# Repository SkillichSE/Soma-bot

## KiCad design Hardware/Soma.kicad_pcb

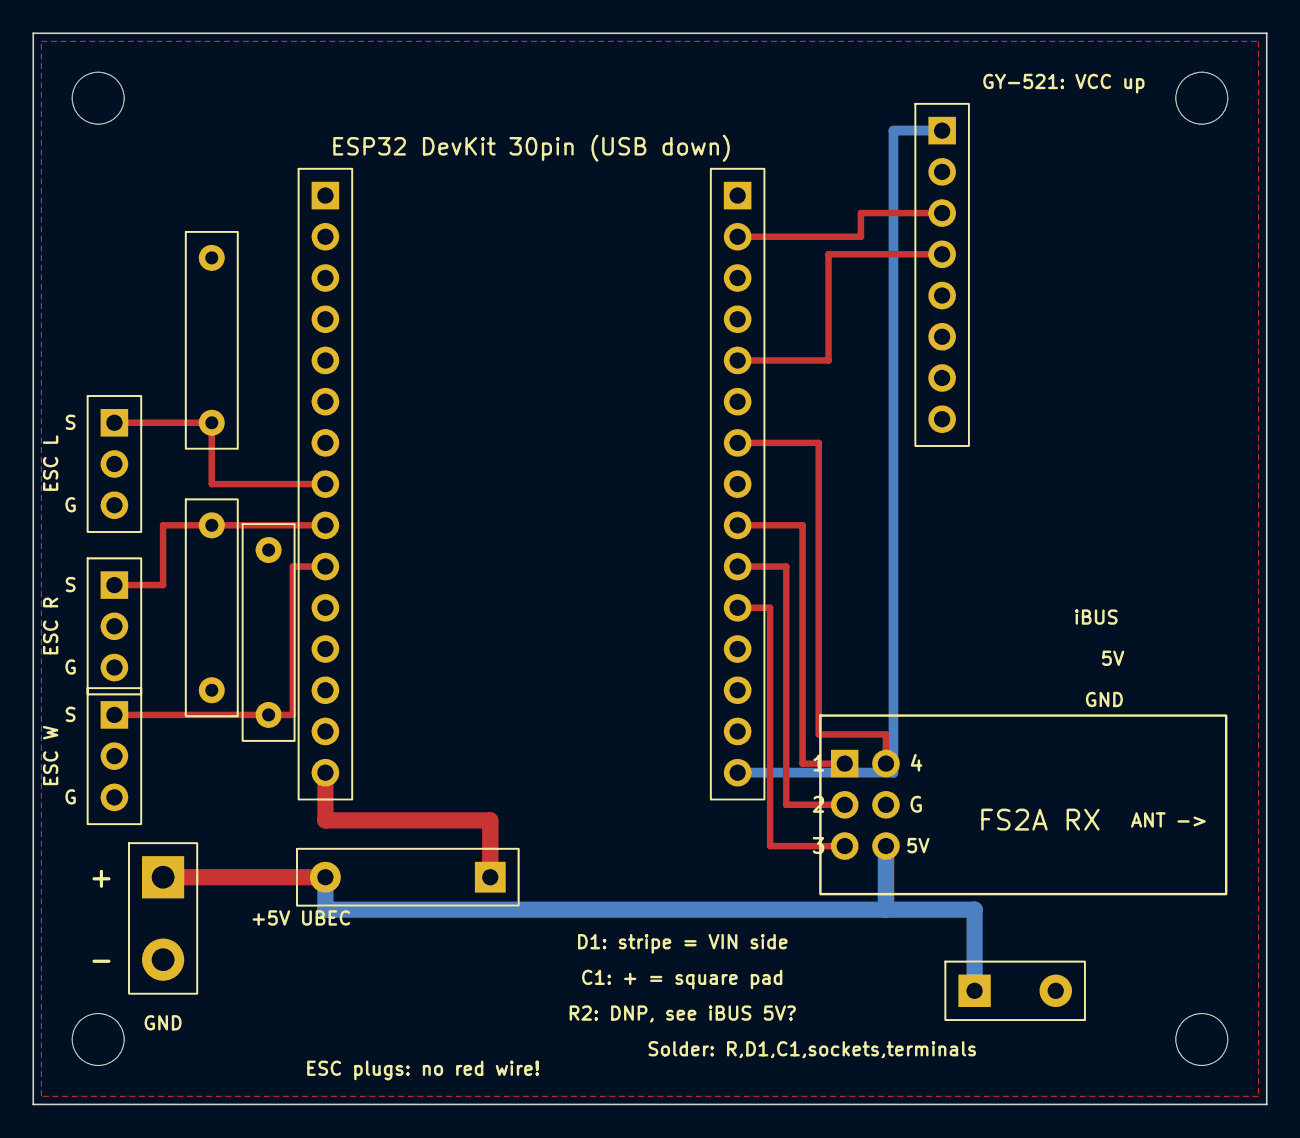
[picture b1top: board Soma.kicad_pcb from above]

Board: 2 copper layers, 76.0 x 66.0 mm, 17 parts (0 on the bottom side), 13 nets.

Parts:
C1: 1000uF; CP_Radial_D10.0mm_P5.00mm
D1: 1N5819 (K=pad1); D_DO-41_SOD81_P10.16mm_Horizontal
H1, H2, H3, H4: M3; MountingHole_3.2mm_M3
J1: UBEC 5V; TerminalBlock_bornier-2_P5.08mm
J3: ESC L; PinHeader_1x03_P2.54mm_Vertical
J4: ESC R; PinHeader_1x03_P2.54mm_Vertical
J5: ESC WEAPON; PinHeader_1x03_P2.54mm_Vertical
R3, R4, R5: 10k; R_Axial_DIN0207_L6.3mm_D2.5mm_P10.16mm_Horizontal
U2: GY-521; PinSocket_1x08_P2.54mm_Vertical
U3: FS2A 4CH RX; FS2A_4CH_Receiver_2x3_P2.54
XL1: ESP32 L; PinSocket_1x15_P2.54mm_Vertical
XR1: ESP32 R; PinSocket_1x15_P2.54mm_Vertical

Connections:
+3V3: U2.1, XR1.15
+5V: C1.1, D1.2, J1.1, U3.6
ESC_L_GPIO25: J3.1, R3.1, XL1.8
ESC_R_GPIO26: J4.1, R4.1, XL1.9
ESC_W_GPIO27: J5.1, R5.1, XL1.10
GND: C1.2, J1.2, J3.3, J4.3, J5.3, R3.2, R4.2, R5.2, U2.2, U3.5, XL1.14, XR1.14
PWM_CH1_GPIO17: U3.1, XR1.9
PWM_CH2_GPIO16: U3.2, XR1.10
PWM_CH3_GPIO4: U3.3, XR1.11
PWM_CH4_GPIO18: U3.4, XR1.7
SCL_GPIO22: U2.3, XR1.2
SDA_GPIO21: U2.4, XR1.5
VIN_ESP: D1.1, XL1.15
